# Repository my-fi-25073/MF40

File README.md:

# MF40 PCB Project

[한국어 README](README.ko.md)

MF40 is my-fi's mini 40% custom keyboard PCB family. The variants share the same general design direction, but differ by horizontal width, column configuration, and bottom-row style.

This repository contains the hardware design files, QMK/VIA firmware source files, and sample plate drawing files for the MF40 PCBs.

## Type

The type indicates the PCB width and layout configuration.

* `12` / `13`: Indicates the horizontal PCB length in Cherry MX unit increments.
* `A`: Indicates a configuration where the horizontal width is fully filled with 1u columns.
* `B`: Indicates a configuration with one fewer column than the `A` configuration at the same horizontal width.
* `W`: Indicates support for a full WK-style bottom row.
* `H`: Indicates support for a 1.125u HHKB-style bottom row.

## Variants

| Variant      | Layout Configuration              | Main Layout Options                                                      |
| ------------ | --------------------------------- | ------------------------------------------------------------------------ |
| `MF40-R12AW` | 12u, 12-column, WK-style layout   | 3-split spacebar, 4.5u, 5u, or 7u spacebar                               |
| `MF40-R13AH` | 13u, 13-column, HHKB-style layout | Split or 2u Backspace, 6.25u or split spacebar                           |
| `MF40-R13AW` | 13u, 13-column, WK-style layout   | Split or 2u Backspace, 6u or split spacebar                              |
| `MF40-R13BW` | 13u, 12-column, WK-style layout   | ANSI/ISO/split/BAE Enter, left/right Shift options, 6u or split spacebar |

## Repository Structure

```text
KicadFiles/       KiCad schematic and PCB files
FirmwareFiles/    QMK/VIA firmware source folders
PlateFiles/       DXF plate drawing files
OtherFiles/       Other project files
```

## Firmware

Each firmware folder under `FirmwareFiles/` corresponds to one PCB variant. To compile the firmware, copy the relevant folder into QMK's `keyboards/` directory.

The firmware supports VIA and custom LED control.

## Hardware

Each PCB variant is managed as an independent KiCad project under `KicadFiles/`. If production outputs are available, they are placed in the `production/` directory of each variant.

## License

See [LICENSE](LICENSE).

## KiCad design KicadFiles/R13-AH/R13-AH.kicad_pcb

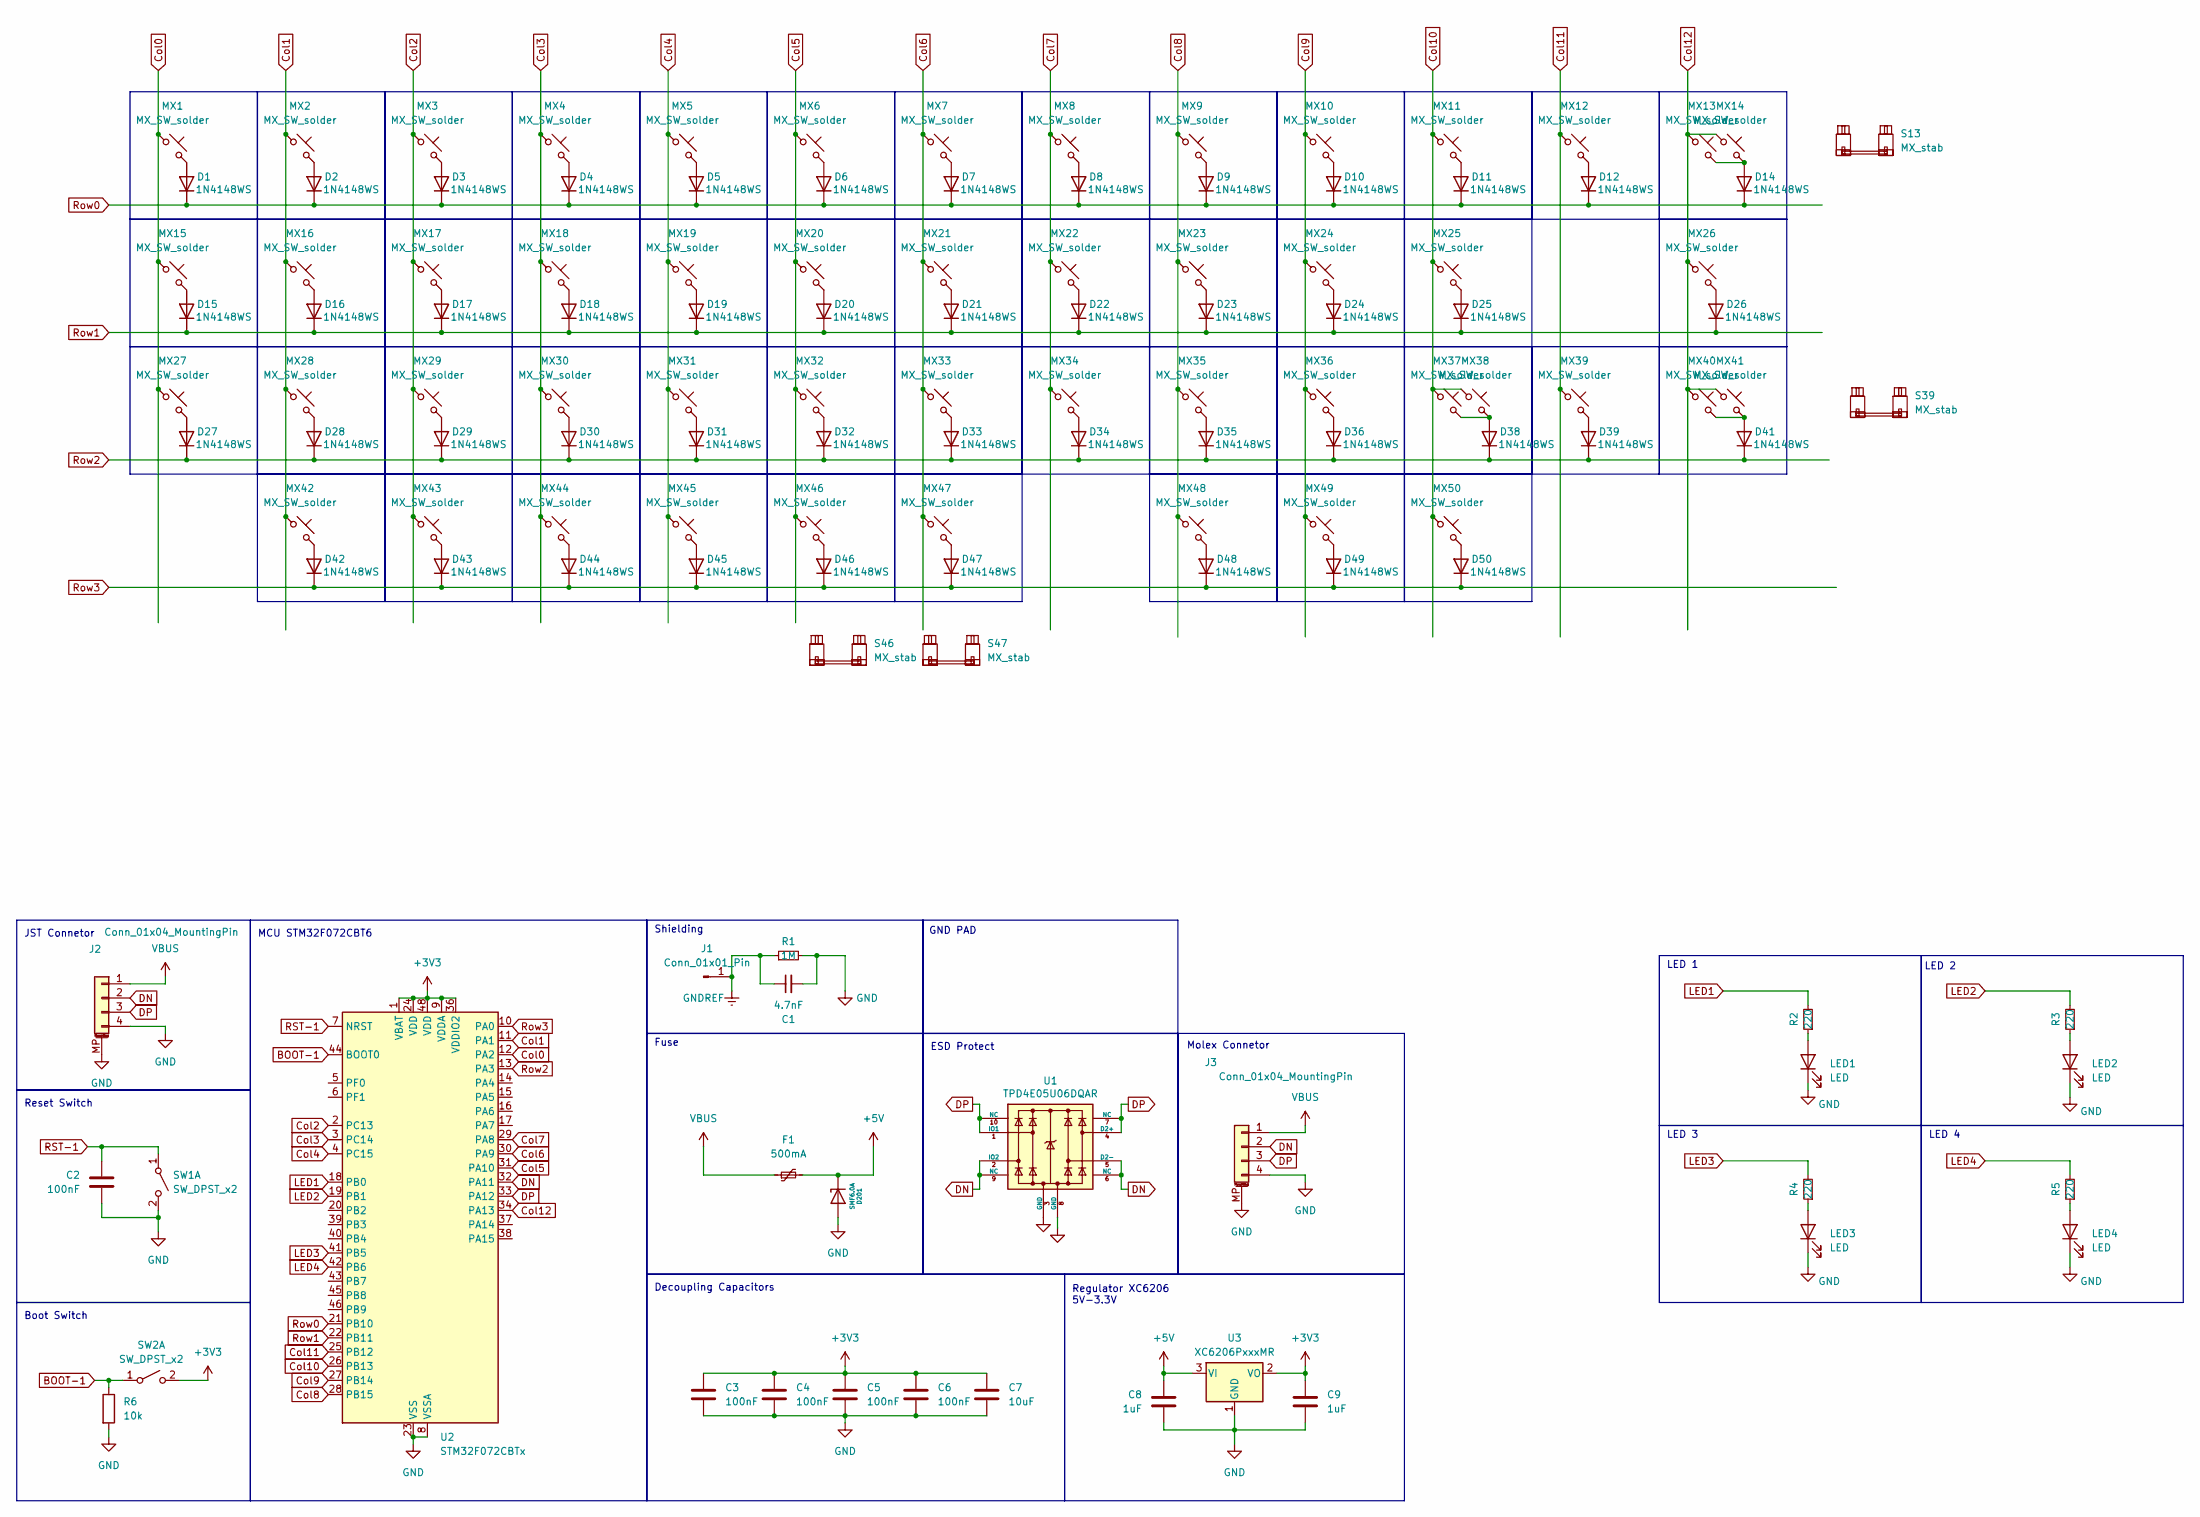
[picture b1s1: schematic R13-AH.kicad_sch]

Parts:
C1: 4.7nF; C_0402_1005Metric
C2, C3, C4, C5, C6: 100nF; C_0402_1005Metric
C7: 10uF; C_0402_1005Metric
C8, C9: 1uF; C_0402_1005Metric
D1, D2, D3, D4, D5, D6, D7, D8, D9, D10, D11, D12, D14, D15, D16, D17, D18, D19, D20, D21, D22, D23, D24, D25, D26, D27, D28, D29, D30, D31, D32, D33, D34, D35, D36, D38, D39, D41, D42, D43, D44, D45, D46, D47, D48, D49, D50: 1N4148WS; D_SOD-323_HandSoldering
D201: SMF6.0A; D_SOD-123; Manufacturer Part Number SMF6.0A; LCSC Part Number C708002
F1: 500mA; Fuse_1206_3216Metric; LCSC C70076
J1: Conn_01x01_Pin; TestPoint_THTPad_2.0x2.0mm_Drill1.0mm
J2: Conn_01x04_MountingPin; JST_SH_SM04B-SRSS-TB_1x04-1MP_P1.00mm_Horizontal
J3: Conn_01x04_MountingPin; Molex_Pico-EZmate_78171-0004_1x04-1MP_P1.20mm_Vertical; Manufacturer Part Number 78171-0004; LCSC Part Number C588524
LED1, LED2, LED3, LED4: LED; DIP_LED_MX_3mm
MX1, MX2, MX3, MX4, MX5, MX6, MX7, MX8, MX9, MX10, MX11, MX12, MX13, MX14, MX16, MX17, MX18, MX19, MX20, MX21, MX22, MX23, MX24, MX25, MX28, MX29, MX30, MX31, MX32, MX33, MX34, MX35, MX36, MX37, MX39, MX41, MX42, MX45, MX46, MX47, MX50: MX_SW_solder; SW_MX_1u
MX15, MX38, MX40, MX43, MX48, MX49: MX_SW_solder; SW_MX_1.25u
MX26, MX27, MX44: MX_SW_solder; SW_MX_1.75u
R1: 1M; R_0402_1005Metric
R2, R3, R4, R5: 220; R_0402_1005Metric
R6: 10k; R_0402_1005Metric
S13, S47: MX_stab; STAB_MX_2u
S39: MX_stab; STAB_MX_2.25u
S46: MX_stab; STAB_MX_6.25u
SW1, SW2: SW_DPST_x2; SW_Push_1P1T_XKB_TS-1187A; MPN C318884
U1: TPD4E05U06DQAR; USON-10_2.5x1.0mm_P0.5mm; Manufacturer Part Number TPD4E05U06DQAR; LCSC Part Number C138714
U2: STM32F072CBTx; LQFP-48_7x7mm_P0.5mm; MPN C81720
U3: XC6206PxxxMR; SOT-23-3; MPN C5148692

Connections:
+3V3: C3.1, C4.1, C5.1, C6.1, C7.1, C9.1, SW2.2 (B), U2.1 (VBAT), U2.9 (VDDA), U2.24 (VDD), U2.36 (VDDIO2), U2.48 (VDD), U3.2 (VO)
+5V: C8.1, D201.1 (K), F1.2, U3.3 (VI)
BOOT-1: R6.1, SW2.1 (A), U2.44 (BOOT0)
Col0: MX1.1, MX15.1, MX27.1, U2.12 (PA2)
Col1: MX2.1, MX16.1, MX28.1, MX42.1, U2.11 (PA1)
Col2: MX3.1, MX17.1, MX29.1, MX43.1, U2.2 (PC13)
Col3: MX4.1, MX18.1, MX30.1, MX44.1, U2.3 (PC14)
Col4: MX5.1, MX19.1, MX31.1, MX45.1, U2.4 (PC15)
Col5: MX6.1, MX20.1, MX32.1, MX46.1, U2.31 (PA10)
Col6: MX7.1, MX21.1, MX33.1, MX47.1, U2.30 (PA9)
Col7: MX8.1, MX22.1, MX34.1, U2.29 (PA8)
Col8: MX9.1, MX23.1, MX35.1, MX48.1, U2.28 (PB15)
Col9: MX10.1, MX24.1, MX36.1, MX49.1, U2.27 (PB14)
Col10: MX11.1, MX25.1, MX37.1, MX38.1, MX50.1, U2.26 (PB13)
Col11: MX12.1, MX39.1, U2.25 (PB12)
Col12: MX13.1, MX14.1, MX26.1, MX40.1, MX41.1, U2.34 (PA13)
DN: J2.2, J3.2, U1.2 (IO2), U1.5 (D2-), U1.6 (NC), U1.9 (NC), U2.32 (PA11)
DP: J2.3, J3.3, U1.1 (IO1), U1.4 (D2+), U1.7 (NC), U1.10 (NC), U2.33 (PA12)
GND: C1.2, C2.2, C3.2, C4.2, C5.2, C6.2, C7.2, C8.2, C9.2, D201.2 (A), J2.4, J2.MP (MountPin), J3.4, J3.MP (MountPin), LED1.1 (K), LED2.1 (K), LED3.1 (K), LED4.1 (K), R1.2, R6.2, SW1.2 (B), U1.3 (GND), U1.8 (GND), U2.8 (VSSA), U2.23 (VSS), U2.35 (VSS), U2.47 (VSS), U3.1 (GND)
GNDREF: C1.1, J1.1, R1.1
LED1: R2.2, U2.18 (PB0)
LED2: R3.2, U2.19 (PB1)
LED3: R4.2, U2.41 (PB5)
LED4: R5.2, U2.42 (PB6)
unnamed: D1.2 (A), MX1.2
unnamed: D2.2 (A), MX2.2
unnamed: D3.2 (A), MX3.2
unnamed: D4.2 (A), MX4.2
unnamed: D5.2 (A), MX5.2
unnamed: D6.2 (A), MX6.2
unnamed: D7.2 (A), MX7.2
unnamed: D8.2 (A), MX8.2
unnamed: D9.2 (A), MX9.2
unnamed: D10.2 (A), MX10.2
unnamed: D11.2 (A), MX11.2
unnamed: D12.2 (A), MX12.2
unnamed: D14.2 (A), MX13.2, MX14.2
unnamed: D15.2 (A), MX15.2
unnamed: D16.2 (A), MX16.2
unnamed: D17.2 (A), MX17.2
unnamed: D18.2 (A), MX18.2
unnamed: D19.2 (A), MX19.2
unnamed: D20.2 (A), MX20.2
unnamed: D21.2 (A), MX21.2
unnamed: D22.2 (A), MX22.2
unnamed: D23.2 (A), MX23.2
unnamed: D24.2 (A), MX24.2
unnamed: D25.2 (A), MX25.2
unnamed: D26.2 (A), MX26.2
unnamed: D27.2 (A), MX27.2
unnamed: D28.2 (A), MX28.2
unnamed: D29.2 (A), MX29.2
unnamed: D30.2 (A), MX30.2
unnamed: D31.2 (A), MX31.2
unnamed: D32.2 (A), MX32.2
unnamed: D33.2 (A), MX33.2
unnamed: D34.2 (A), MX34.2
unnamed: D35.2 (A), MX35.2
unnamed: D36.2 (A), MX36.2
unnamed: D38.2 (A), MX37.2, MX38.2
unnamed: D39.2 (A), MX39.2
unnamed: D41.2 (A), MX40.2, MX41.2
unnamed: D42.2 (A), MX42.2
unnamed: D43.2 (A), MX43.2
unnamed: D44.2 (A), MX44.2
unnamed: D45.2 (A), MX45.2
unnamed: D46.2 (A), MX46.2
unnamed: D47.2 (A), MX47.2
unnamed: D48.2 (A), MX48.2
unnamed: D49.2 (A), MX49.2
unnamed: D50.2 (A), MX50.2
unnamed: LED1.2 (A), R2.1
unnamed: LED2.2 (A), R3.1
unnamed: LED3.2 (A), R4.1
unnamed: LED4.2 (A), R5.1
RST-1: C2.1, SW1.1 (A), U2.7 (NRST)
Row0: D1.1 (K), D2.1 (K), D3.1 (K), D4.1 (K), D5.1 (K), D6.1 (K), D7.1 (K), D8.1 (K), D9.1 (K), D10.1 (K), D11.1 (K), D12.1 (K), D14.1 (K), U2.21 (PB10)
Row1: D15.1 (K), D16.1 (K), D17.1 (K), D18.1 (K), D19.1 (K), D20.1 (K), D21.1 (K), D22.1 (K), D23.1 (K), D24.1 (K), D25.1 (K), D26.1 (K), U2.22 (PB11)
Row2: D27.1 (K), D28.1 (K), D29.1 (K), D30.1 (K), D31.1 (K), D32.1 (K), D33.1 (K), D34.1 (K), D35.1 (K), D36.1 (K), D38.1 (K), D39.1 (K), D41.1 (K), U2.13 (PA3)
Row3: D42.1 (K), D43.1 (K), D44.1 (K), D45.1 (K), D46.1 (K), D47.1 (K), D48.1 (K), D49.1 (K), D50.1 (K), U2.10 (PA0)
VBUS: F1.1, J2.1, J3.1

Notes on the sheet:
Regulator XC6206 5V-3.3V
Molex Connetor
ESD Protect
JST Connetor
GND PAD
LED 2
Boot Switch
LED 1
Decoupling Capacitors
LED 4
MCU STM32F072CBT6
LED 3
Fuse
Reset Switch
Shielding

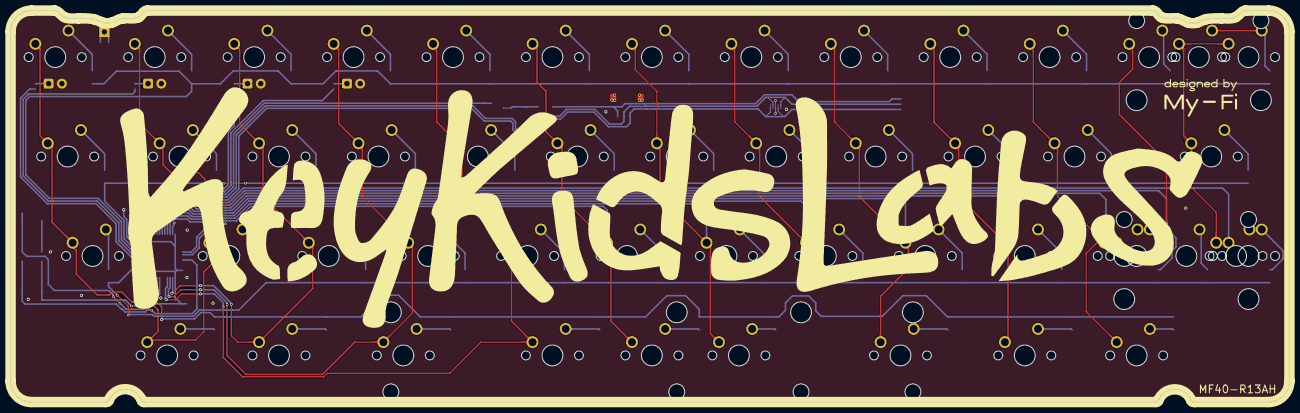
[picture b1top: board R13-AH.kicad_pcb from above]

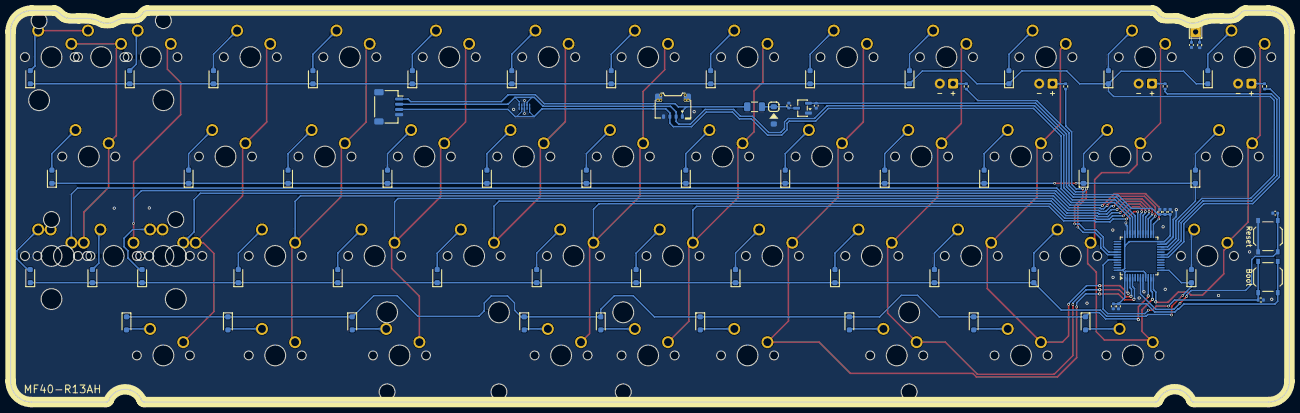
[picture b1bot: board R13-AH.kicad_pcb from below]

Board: 2 copper layers, 245.0 x 75.0 mm, 130 parts (72 on the bottom side), 81 nets.

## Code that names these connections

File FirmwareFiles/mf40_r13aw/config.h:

#pragma once

// LED Pins: B0(LED1), B1(LED2), B5(LED3), B6(LED4)

// // LED Indicators 설정
// #define LED_1_PIN B0
// #define LED_2_PIN B1
// #define LED_3_PIN B5
// #define LED_4_PIN B6

// // LED가 켜질 때의 핀 상태 (1: HIGH, 0: LOW)
// #define LED_PIN_ON_STATE 1

/* 백라이트 설정 - 현재 비활성화 */
// #define BACKLIGHT_PIN A6
// #define BACKLIGHT_LEVELS 1

#define DYNAMIC_KEYMAP_LAYER_COUNT 6
#define VIA_EEPROM_CUSTOM_CONFIG_SIZE 32
#define EECONFIG_KB_DATA_SIZE VIA_EEPROM_CUSTOM_CONFIG_SIZE
#define VIA_FIRMWARE_VERSION 0x00000001

#define USB_POLLING_INTERVAL_MS 1

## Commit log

2026-04-15 Add README overview for MF40 PCB project
2026-04-16 Add keyboard layout JSON files for 12u and 13u configurations
    - Created 12u-40p-keyboard-layout.json with detailed key specifications.
    - Created 13u-40p-keyboard-layout.json with comprehensive key dimensions and attributes.
2026-04-27 Add and update KiCad design assets for R12/R13 variants
    - refresh existing R12-AW, R13-AH, and R13-BW project files
    - add the R13-AW project and variant-specific placer configs
    - add 12u/13u outlines and normalize layout JSON filenames
2026-04-28 Add junctions and wires to R13-BW schematic for improved connectivity
    - Added a junction at (300.99, 62.23) to enhance signal routing.
    - Introduced a junction at (306.07, 67.31) for better circuit integration.
    - Removed unnecessary junction at (299.72, 44.45) to clean up the schematic.
    - Updated wire connections to reflect new junction placements and maintain circuit integrity.
2026-04-28 Implement feature X to enhance user experience and optimize performance
2026-04-28 Refactor code structure for improved readability and maintainability
2026-04-29 Add global labels for columns and rows in R13-AH schematic
    - Introduced new global labels for columns (Col0 to Col12) and rows (Row0 to Row3) in the R13-AH schematic.
    - Each label includes properties for intersheet references, font size, justification, and positioning.
    - Enhanced organization and readability of the schematic by clearly defining input and output connections.
2026-05-03 Update DRC exclusions and modify error handling in R13-AH.kicad_pro
    - Added multiple DRC exclusions for specific footprints and hole clearances.
    - Changed DRC error handling settings for courtyards overlap, hole to hole, nonmirrored text on back layer, silk edge clearance, silk over copper, and silk overlap to "ignore".
    - Updated solder mask to copper clearance from 0.0 to 0.005.
2026-05-05 Update design rules and add global labels in schematic
    - Changed design rule for "courtyards_overlap" from "error" to "ignore".
    - Updated hole clearance and hole to hole rules to "ignore".
    - Set several silk layer rules to "ignore" to reduce warnings.
    - Added multiple global labels in the schematic for better intersheet referencing, including "Col0", "Col1", "Col2", "Col3", "Col4", "Col5", "Col6", "Col7", "Col8", "Col9", "Col10", "Col11", "Col12",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
2026-05-06 Update design rules and add global labels in schematic
    - Changed design rule settings in R13-AW.kicad_pro to ignore several warnings and errors, including courtyard overlaps, hole clearance, silk edge clearance, and solder mask bridges.
    - Added multiple global labels in R13-AW.kicad_sch for better intersheet referencing, including Col0, Col1, Col2, Col3, Col4, Col5, Col6, Col7, Col8, Col9, Col10, Col11, Col12, Row0, Row1, Row2, and 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
    - Ensured proper placement and formatting for new global labels to enhance readability and maintainability of the schematic.
2026-05-16 Add custom keycodes and LED effects for MF40-R12AW keyboard
    - Implemented custom keycodes for various OS shortcuts including language switch, screenshot capture, and desktop navigation.
    - Created my_effect.h and my_effect.c for LED effect management, including typing hold, breathing, and indicator modes.
    - Defined keymap layers and custom keycodes in my_keycode.h for better keyboard functionality.
    - Added readme.md for project documentation and flashing instructions.
    - Configured rules.mk to enable VIA and OS detection features.
    - Created vi.json and via.json for visual representation and configuration of the keyboard layout and LED effects.
2026-05-16 Add custom keycodes and LED effects for MF40-R13AH keyboard
    - Created my_effect.h and my_effect.c for LED effect management.
    - Implemented my_keycode.c and my_keycode.h for custom keycode handling.
    - Added rules.mk to enable VIA and OS detection features.
    - Included vi.json and via.json for keyboard layout and configuration.
    - Added a readme.md for project documentation and build instructions.
2026-05-16 Implement feature X to enhance user experience and fix bug Y in module Z
2026-05-16 Add custom keycode functionality and supporting files for MF40-R13AW keyboard
    - Implemented custom keycodes in my_keycode.c for various OS-specific actions including language switching, screenshot capture, and desktop navigation.
    - Defined custom keycodes in my_keycode.h for easy reference and usage.
    - Created a readme.md file to provide project overview, build instructions, and bootloader entry methods.
    - Configured rules.mk to enable VIA and OS detection, and included custom source files.
    - Added vi.json and via.json files for visual representation and configuration of the keyboard layout and keycodes in VIA.
2026-05-16 Add custom keycodes and configuration for MF40-R13BW keyboard
    - Created my_keycode.h to define custom keycodes and layers.
    - Added a readme.md file with project description and build instructions.
    - Introduced rules.mk to enable VIA and OS detection features.
    - Added vi.json for visual representation of the keyboard layout.
    - Created via.json for VIA configuration including custom keycodes and LED effects.
2026-06-18 Enhance design settings in R13-BW project
    - Added options to disable default application for footprint barcodes and dimensions.
    - Updated zone settings with additional parameters including border display style, corner radius, and thermal relief specifications.
    - Introduced new warnings for footprint symbol field mismatches and missing tuning profiles.
    - Adjusted track settings to include new ignore rules for centered tracks and tuning profile geometries.
2026-06-18 Add Korean README translation and enhance project documentation
